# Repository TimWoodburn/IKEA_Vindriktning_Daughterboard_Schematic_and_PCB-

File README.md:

# IKEA_Vindriktning_Daughterboard_Schematic_and_PCB

## Prelude - design choices before this project.
After reading about the IKEA sensor in Hackaday <https://hackaday.com/2021/08/13/hacked-ikea-air-quality-sensor-gets-custom-pcb/> I embarked on implementing on my favourite Wifi connected microcontroller ESP8266 with a view to adding additional sensors.  My usual preference is to roll-my-own, but during my research I became aware of a couple of implementations that utilized Tasmota.  This is an ideal platform to satisfy this requirement.  Web front end, MQTT ready, community maintained and includes the peripherals I was interested in; namely BME280 and LDR and the Ikea particulate sensor.  

This project is an adoptation based on Lond's Hackaday.io project, https://hackaday.io/project/181195-ikea-vindriktning-pcb and
Catalin Sanda who provided their schematics, https://hackaday.io/project/184282-ikea-vindriktning-daughterboard  

Blakadder has a nice write up.  The Tasmota setup is applicable to this project https://blakadder.com/vindriktning-tasmota/

If you dont wish to use Tasmota, checkout Hypfer's implements decoding of the Ikea sensor directly https://github.com/Hypfer/esp8266-vindriktning-particle-sensor

## Project Details

This project adds BME280 and Light Dependent resistor and uses Catalin Sanda's Tasmota binary.

The project uses the following ESP8266 ports:
- GPIO 4 for the Ikea particulate sensor input
- GPIO 1 for FTDI TXD
- GPIO 3 for FTDI RXD
- GPIO 12 for I2C SCL
- GPIO 14 for I2C SDA
- ADC for LDR input

## IKEA Vindriktning Daughterboard Schematic

A slight modification of Catalin Sanda's design on <https://hackaday.io/project/184282-ikea-vindriktning-daughterboard> which adds an input for a light dependent resistor into the ADC.  I have also chosen to use different inputs.  I also added the Molex picoblade sockets as suggested by Lond's project <https://hackaday.io/project/181195-ikea-vindriktning-pcb>.  The looms were challenging to work with and took some time to get right.  The Molex picoblade connectors look beautiful, but the crimps are tiny and practice makes perfect in getting them right.  If I did this project from scratch again, I would purchase pre-crimped plugs and then terminate the tails.  I bought a cheap crimp tool so I am sure the experience with the £200 ratcheted Molex crimp tool is far better, but it was too expensive for this project.

## Modification of the IKEA Vindriktning PCB

The designers were very generous in making the board accessible to makers.  In order to use connect the daughterboard neatly, a 5 way Molex SMD socket should be soldered to the board (pictured on the LHS of the board).  As others have done in their solutions, it is possible to solder directly to the board.

The light dependent resistor is fitted to the fascia as pictured and terminals insulated.  I kept the BME280 loose to allow for placement away from the fascia in the other half of the enclosure.  

## Daughterboard

Pictured as received from JLCPCB.  Note R9 pictured reflects the BOM error which fitted a 2R2 resistor, rather than 220K0. The repo BOM has been corrected.

I copied the Caralin's flashing method and will use the same method in future boards.  The PRG pin is shorted to ground away from the board.  I bought mine from AliExpress which seems to work quite well [LINK](https://www.aliexpress.com/item/1005001409579446.html)  I flashed the boards with Tazmotizer with the version that contains the Vindriktning peripheral.  Alternatively use [tasmota-allsensors unoffical build](https://github.com/tasmota/install/raw/main/firmware/unofficial/tasmota-allsensors.bin) although this is untested.  The version I used is within this repo.

The spring in the laced BME280 loom positions the board out of the way.  Once you have tested, you may wish to secure it.  The board itself slides behind the screw pillars.

## Tasmota Setup 

Once fitted, configure the module as follows.

Which should generate a home page like this.

To change the device name, go to the "other options" page and set there.

## In use

I use mine with my other house sensors signalled with MQTT.  My MQTT setup uses Mosquitto and NODERED.  

The data is stored in an InfluxDB 3.x database and viewed on Grafana.  The garage peak is probably due to me sweeping up after completing this project!

## How to order populated PCB with JLCPCB
[Phil's Lab - Kicad design and JLCPCB Assembly for ordering this board.](https://www.youtube.com/watch?v=C7-8nUU6e3E&t=9415s)
1. Go to [JLCPCB](https://jlcpcb.com/") and log in.
2. Click on "Instant quote".
3. Upload the zipped gerber.
4. Review the board parameters (you may click remove order number if you wish).
5. Click PCB assembly.
6. Click Tooling Holes "Added by Cuastomer" and agree the T&C if you are happy with them.
7. Click confirm.
8. Click "Add BOM File", browse for IKEA_Vindriktning_Daughterboard-TW_bom.xls file in the assembly directory.
9. Click "Add CPL", browse for IKEA_Vindriktning_Daughterboard-all-pos.xls file in the assembly directory.
10. Select Sensor/Controller/Precision Instrument/Temperature sensor" or similar in the description combobox, probably for customs declarations.
11. Check the matched part detail, especially the values and if they are in stock.  You may have to search for alternative parts if there are none in stock.  Check the footprints of alternatives.
12. Click next.
13. The review parts placement window will probably show incorrect rotation on some parts, this will be checked and corrected by JLCPCB.
14. Save to cart and order.

## Vindriktning Links  
[Catlalin Sanda Hackaday.io blog post](https://hackaday.io/project/184282-ikea-vindriktning-daughterboard)  
[Lond's Hackaday.io blog post](https://hackaday.io/project/181195-ikea-vindriktning-pcb)  
[Blakadder's IKEA Vindriktning air quality sensor running Tasmota](https://blakadder.com/vindriktning-tasmota/)  
[Hypfer/esp8266-vindriktning-particle-sensor](https://github.com/Hypfer/esp8266-vindriktning-particle-sensor)  
[Vccground implementation - #34 VINDRIKTNING | Modifying to the next level as Standalone / Home Assistant Connected Multi Sensor ](https://www.youtube.com/watch?v=BSLXqhjjSZI) includes a schematic of the Ikea board.  

## Other Links  
[Tasmota Home](https://tasmota.github.io/docs/)  
[tasmota-allsensors unoffical build](https://github.com/tasmota/install/raw/main/firmware/unofficial/tasmota-allsensors.bin)  
[Phil's Lab - Kicad design and JLCPCB Assembly for ordering this board.](https://www.youtube.com/watch?v=C7-8nUU6e3E&t=9415s)

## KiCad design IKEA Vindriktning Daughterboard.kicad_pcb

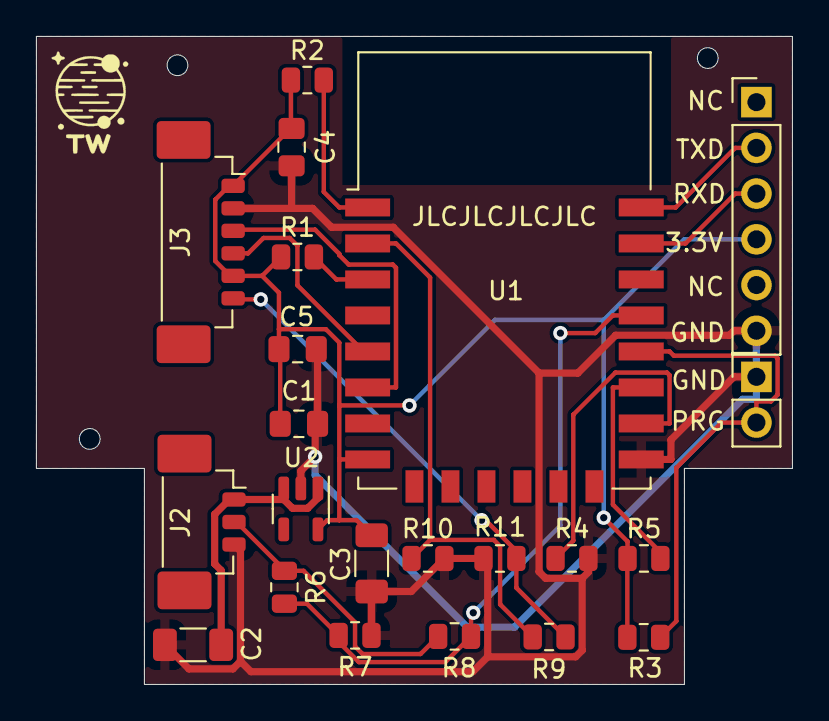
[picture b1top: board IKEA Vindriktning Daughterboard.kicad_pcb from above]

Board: 2 copper layers, 42.0 x 36.0 mm, 22 parts (0 on the bottom side), 16 nets.

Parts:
C1, C4, C5: 330nF; C_0805_2012Metric_Pad1.18x1.45mm_HandSolder
C2: 1.0µF; C_1206_3216Metric_Pad1.33x1.80mm_HandSolder
C3: 1.0uF; C_1206_3216Metric_Pad1.33x1.80mm_HandSolder
J1: FTDI Connector; PinHeader_1x06_P2.54mm_Vertical
J2: Conn_01x03_Male; Molex_PicoBlade_53398-0371_1x03-1MP_P1.25mm_Vertical
J3: CJMCU-680; Molex_PicoBlade_53398-0671_1x06-1MP_P1.25mm_Vertical
J4: Conn_01x02_Male; PinHeader_1x02_P2.54mm_Vertical
R1, R2, R3, R4, R5, R6, R7, R8, R11: 10K; R_0805_2012Metric
R9: 220K; R_0805_2012Metric
R10: 100K; R_0805_2012Metric
U1: ESP-12F; ESP-12E
U2: AP2202-3V3; SOT-23-5

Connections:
+5V: C2.1, J2.1, U2.1 (VIN), U2.3 (EN)
ADC: R9.2, R10.1, U1.2 (ADC)
GND: C1.2, C2.2, C3.2, C4.2, C5.2, J1.6, J2.3, J3.2, J4.1, R4.2, R7.2, R10.2, R11.2, U1.15 (GND), U2.2 (GND)
LDR_A: C1.1, C3.1, C4.1, C5.1, J1.4, J3.1, J3.5, R1.1, R2.1, R3.1, R5.1, U1.8 (VCC), U2.5 (VOUT)
LDR_B: J3.6, R9.1, R11.1
unnamed: J2.2, R6.1, R8.1
unnamed: J4.2, R3.2, U1.18 (GPIO0)
unnamed: R1.2, U1.3 (EN)
unnamed: R2.2, U1.1 (~RST)
unnamed: R4.1, U1.16 (GPIO15)
unnamed: R5.2, U1.17 (GPIO2)
RXD: J1.3, U1.21 (GPIO3/RXD)
SCL: J3.3, U1.6 (GPIO12)
SDA: J3.4, U1.5 (GPIO14)
SensorIn: R6.2, R7.1, R8.2, U1.19 (GPIO4)
TXD: J1.2, U1.22 (GPIO1/TXD)

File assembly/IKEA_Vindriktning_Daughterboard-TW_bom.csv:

Comment,Designator,Footprint,LCSC
330nF,"C1,C4,C5",Capacitor_SMD:C_0805_2012Metric_Pad1.18x1.45mm_HandSolder,C1775
1.0µF,C2,Capacitor_SMD:C_1206_3216Metric_Pad1.33x1.80mm_HandSolder,C1848
1.0uF,C3,Capacitor_SMD:C_1206_3216Metric_Pad1.33x1.80mm_HandSolder,C1848
FTDI Connector,J1,Connector_PinHeader_2.54mm:PinHeader_1x06_P2.54mm_Vertical,
Conn_01x03_Male,J2,Connector_Molex:Molex_PicoBlade_53398-0371_1x03-1MP_P1.25mm_Vertical,C293633
CJMCU-680,J3,Connector_Molex:Molex_PicoBlade_53398-0671_1x06-1MP_P1.25mm_Vertical,C277393
Conn_01x02_Male,J4,Connector_PinHeader_2.54mm:PinHeader_1x02_P2.54mm_Vertical,
10K,"R1,R2,R3,R4,R5,R6,R7,R8,R11",Resistor_SMD:R_0805_2012Metric,C17414
100K,R10,Resistor_SMD:R_0805_2012Metric,C149504
220K,R9,Resistor_SMD:R_0805_2012Metric,C17556
ESP-12F,U1,RF_Module:ESP-12E,Copy
AP2202-3V3,U2,Package_TO_SOT_SMD:SOT-23-5,C150442

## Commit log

2022-06-12 initial v1.0.1 upload
